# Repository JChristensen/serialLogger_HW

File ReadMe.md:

# Serial Data Logger #

An Arduino-compatible logger that writes all serial data input on digital pin 0 (RXD) to a micro SD card. Firmware for the Serial Logger is at [https://github.com/JChristensen/serialLogger](https://github.com/JChristensen/serialLogger). A bill of materials is [available on Mouser.com](http://www.mouser.com/ProjectManager/ProjectDetail.aspx?AccessID=75ac867039).

The firmware can be programmed directly with an ICSP programmer or via a bootloader (use the standard Arduino Uno Optiboot bootloader). Before programming this board with an ICSP programmer, ensure that the SD card is removed.

The Serial Logger board can be powered in several ways:
- Via the FTDI header. This is handy if the MCU being logged uses 5V power.
- Via the power jack. Either 5V regulated or 7-12V can be connected to the jack. First ensure that the four-pin PWR SEL header is jumpered to match the input voltage.
- Via the four-pin PWR SEL header. Remove the jumper and connect either 5V regulated or 7-12V to the like-labeled pin. A ground pin is also provided on the PWR SEL header.

### Revision History ###

**16Oct2014 v2.0** -- Custom PC board, initial version.

### CC BY-SA ###
Serial Data Logger by Jack Christensen is licensed under CC BY-SA 4.0, http://creativecommons.org/licenses/by-sa/4.0/

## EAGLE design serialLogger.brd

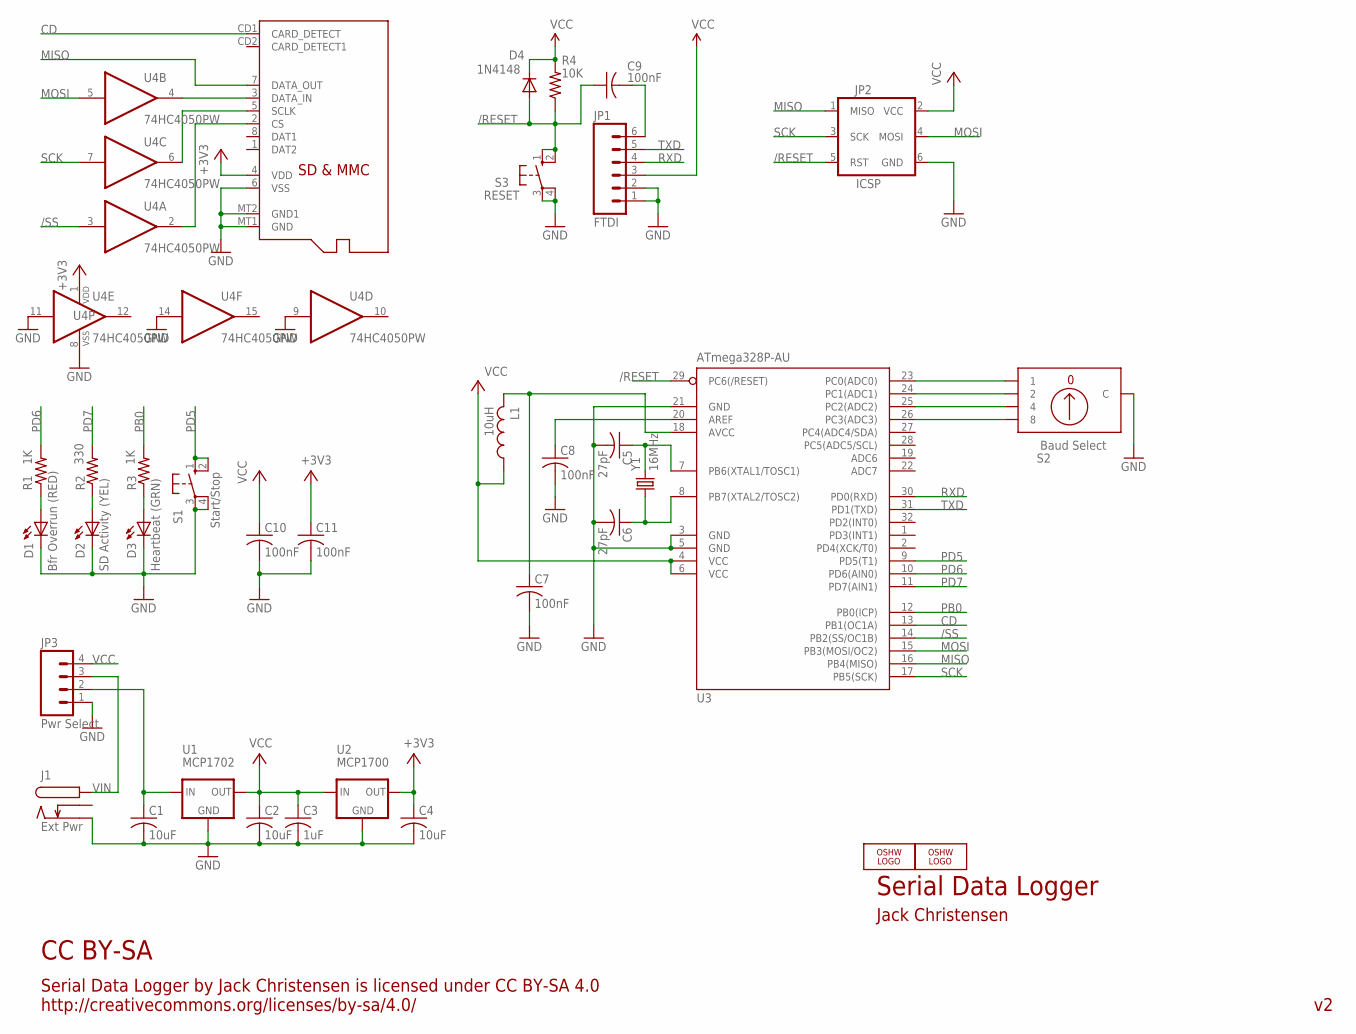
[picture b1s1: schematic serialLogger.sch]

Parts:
C1, C2, C4: 10uF; M0805
C3: 1uF; M0805
C5, C6: 27pF; M0805
C7, C8, C9, C10, C11: 100nF; M0805
D1: Bfr Overrun (RED); CHIPLED_1206
D2: SD Activity (YEL); CHIPLED_1206
D3: Heartbeat (GRN); CHIPLED_1206
D4: 1N4148; SOD-323F-A
J1: Ext Pwr; KLDX-0202
JP1: FTDI; 1X06_LOCK
JP2: ICSP; 2X3_LOCK
JP3: Pwr Select; 1X04_LOCK
L1: 10uH; M0805
LOGO1, LOGO2: OSHW_LOGO_10MILX0200-NT; OSHW_10X200_NOTEXT
R1, R3: 1K; M0805
R2: 330; M0805
R4: 10K; M0805
S1: Start/Stop; B3F-10XXOCT
S2: Baud Select; OMRON-A6RS-102
S3: RESET; B3F-10XXOCT
U1: MCP1702; SOT89
U2: MCP1700; SOT23
U3: ATmega328P-AU; TQFP32-08
U4: 74HC4050PW; TSSOP16
X1: MICROSD
Y1: 16MHz; CRYSTAL-ABRACON-ABM2

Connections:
+3V3: C4.1, C11.1, U2.2 (OUT), U4.1 (VDD), X1.4 (VDD)
/RESET: C9.1, D4.A, JP2.5 (RST), R4.1, S3.1 (S), S3.2 (S1), U3.29 (PC6(/RESET))
/SS: U3.14 (PB2(SS/OC1B)), U4.3 (I)
CD: U3.13 (PB1(OC1A)), X1.CD1 (CARD_DETECT)
GND: C1.2, C2.2, C3.2, C4.2, C5.2, C6.2, C7.2, C8.2, C10.2, C11.2, D1.C, D2.C, D3.C, J1.P$2, JP1.1, JP1.2, JP2.6 (GND), JP3.1, S1.3, S1.4 (P1), S2.C.1 (C), S2.C.2 (C), S3.3, S3.4 (P1), U1.1 (GND), U2.1 (GND), U3.3 (GND), U3.5 (GND), U3.21 (GND), U4.8 (VSS), U4.9 (I), U4.11 (I), U4.14 (I), X1.6 (VSS), X1.MT1 (GND), X1.MT2 (GND1)
MISO: JP2.1 (MISO), U3.16 (PB4(MISO)), X1.7 (DATA_OUT)
MOSI: JP2.4 (MOSI), U3.15 (PB3(MOSI/OC2)), U4.5 (I)
unnamed: D3.A, R3.1
unnamed: D2.A, R2.1
unnamed: D1.A, R1.1
unnamed: C1.1, JP3.2, U1.2 (IN), U1.2.1 (IN)
unnamed: S2.1, U3.23 (PC0(ADC0))
unnamed: S2.2, U3.24 (PC1(ADC1))
unnamed: S2.4, U3.25 (PC2(ADC2))
unnamed: S2.8, U3.26 (PC3(ADC3))
unnamed: U4.6 (O), X1.5 (SCLK)
unnamed: U4.2 (O), X1.2 (CS)
unnamed: U4.4 (O), X1.3 (DATA_IN)
unnamed: C5.1, U3.7 (PB6(XTAL1/TOSC1)), Y1.P$2 (2)
unnamed: C6.1, U3.8 (PB7(XTAL2/TOSC2)), Y1.P$1 (1)
unnamed: C8.1, U3.20 (AREF)
unnamed: C7.1, L1.2, U3.18 (AVCC)
PB0: R3.2, U3.12 (PB0(ICP))
PD5: S1.1 (S), S1.2 (S1), U3.9 (PD5(T1))
PD6: R1.2, U3.10 (PD6(AIN0))
PD7: R2.2, U3.11 (PD7(AIN1))
RST: C9.2, JP1.6
RXD: JP1.4, U3.30 (PD0(RXD))
SCK: JP2.3 (SCK), U3.17 (PB5(SCK)), U4.7 (I)
TXD: JP1.5, U3.31 (PD1(TXD))
VCC: C2.1, C3.1, C10.1, D4.K, JP1.3, JP2.2 (VCC), JP3.4, L1.1, R4.2, U1.3 (OUT), U2.3 (IN), U3.4 (VCC), U3.6 (VCC)
VIN: J1.P$1, JP3.3

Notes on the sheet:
Serial Data Logger
Jack Christensen
Serial Data Logger by Jack Christensen is licensed under CC BY-SA 4.0 http://creativecommons.org/licenses/by-sa/4.0/
CC BY-SA

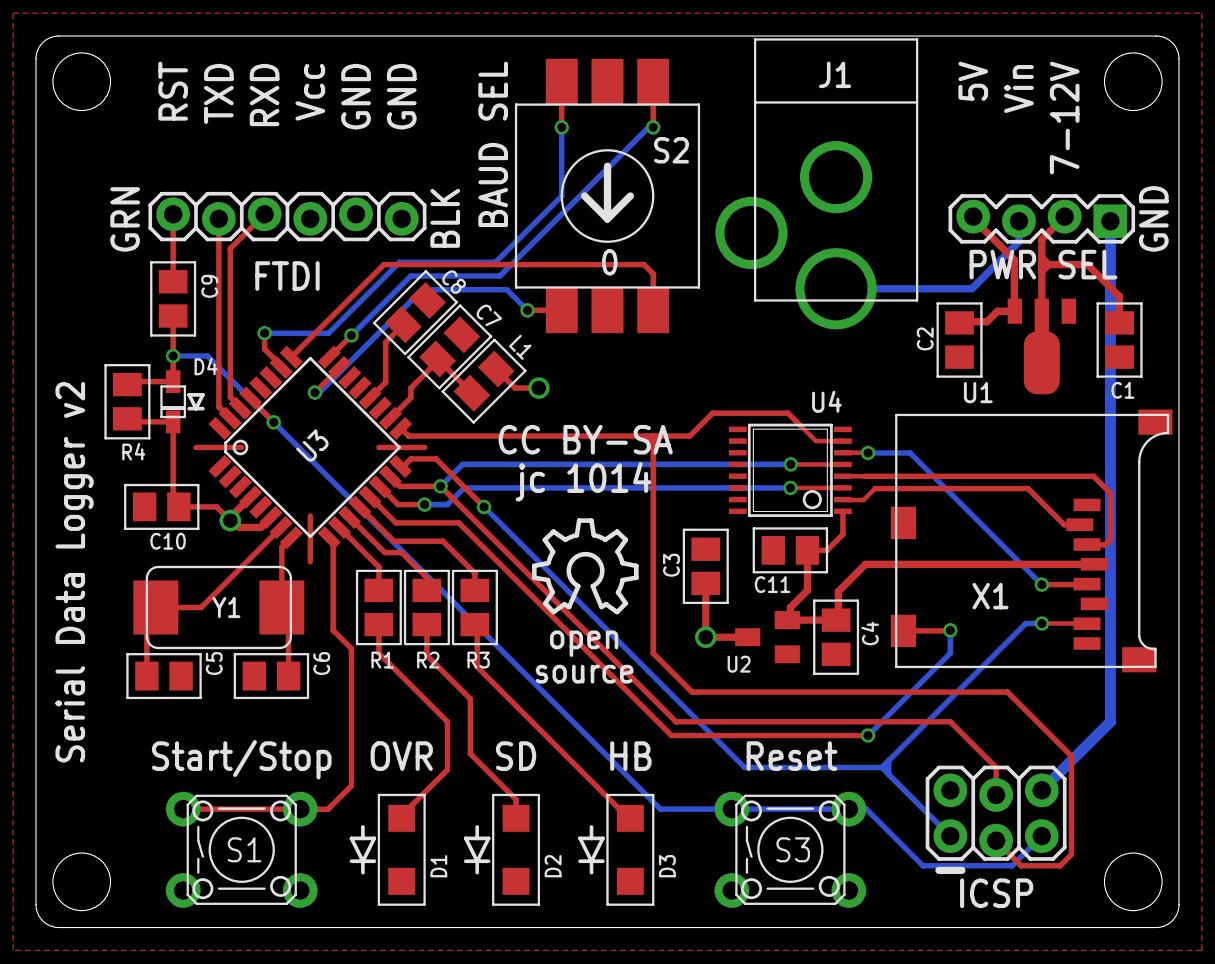
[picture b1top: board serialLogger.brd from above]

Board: 2 copper layers, 63.5 x 49.5 mm, 35 parts (1 on the bottom side), 32 nets.

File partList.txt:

Partlist

Exported from serialLogger.sch at 11/10/2014 7:54:04 PM

EAGLE Version 6.4.0 Copyright (c) 1988-2013 CadSoft

Assembly variant: 

Part     Value             Device                Package              Library  Sheet

C1       10uF              C-USM0805             M0805                _jc      1
C2       10uF              C-USM0805             M0805                _jc      1
C3       1uF               C-USM0805             M0805                _jc      1
C4       10uF              C-USM0805             M0805                _jc      1
C5       27pF              C-USM0805             M0805                _jc      1
C6       27pF              C-USM0805             M0805                _jc      1
C7       100nF             C-USM0805             M0805                _jc      1
C8       100nF             C-USM0805             M0805                _jc      1
C9       100nF             C-USM0805             M0805                _jc      1
C10      100nF             C-USM0805             M0805                _jc      1
C11      100nF             C-USM0805             M0805                _jc      1
D1       Bfr Overrun (RED) LEDCHIPLED_1206       CHIPLED_1206         _jc      1
D2       SD Activity (YEL) LEDCHIPLED_1206       CHIPLED_1206         _jc      1
D3       Heartbeat (GRN)   LEDCHIPLED_1206       CHIPLED_1206         _jc      1
D4       1N4148            DIODESOD-323F-A       SOD-323F-A           _jc      1
J1       Ext Pwr           POWER-JACK            KLDX-0202            _jc      1
JP1      FTDI              M06LOCK               1X06_LOCK            SparkFun 1
JP2      ICSP              AVR_SPI_PRG_62X3_LOCK 2X3_LOCK             _jc      1
JP3      Pwr Select        M04LOCK               1X04_LOCK            SparkFun 1
L1       10uH              INDUCTORM0805         M0805                _jc      1
R1       1K                R-US_M0805            M0805                _jc      1
R2       330               R-US_M0805            M0805                _jc      1
R3       1K                R-US_M0805            M0805                _jc      1
R4       10K               R-US_M0805            M0805                _jc      1
S1       Start/Stop        10-XXOCT              B3F-10XXOCT          _jc      1
S2       Baud Select       OMRON-A6RS-102        OMRON-A6RS-102       _jc      1
S3       RESET             10-XXOCT              B3F-10XXOCT          _jc      1
U1       MCP1702           MCP1700SOT89          SOT89                _jc      1
U2       MCP1700           MCP1700SOT23          SOT23                _jc      1
U3       ATmega328P-AU     MEGA8-AI              TQFP32-08            atmel    1
U4       74HC4050PW        4050PW                TSSOP16              40xx     1
X1       MICROSD           MICROSD               MICROSD              adafruit 1
Y1       16MHz             CRYSTALABM2           CRYSTAL-ABRACON-ABM2 _jc      1

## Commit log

2014-10-08 Initial commit, breadboard version.
2014-10-11 Initial v2 board.
2014-10-11 Change to Abracon xtal, refine board, add BOM spreadsheet.
2014-11-11 Final v2 board
2014-11-23 Add LICENSE file.

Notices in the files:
serialLogger.brd:
CC BY-SA jc 1014
parts and their libraries:
SparkFun: Licensing: CC v3.0 Share-Alike You are welcome to use this library for commercial purposes.
